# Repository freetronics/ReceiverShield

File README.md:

Freetronics 315MHz / 433MHz Receiver Shield
===========================================
Copyright 2011 Freetronics Pty Ltd  
Freetronics site:  <www.freetronics.com>  
Freetronics email: <info@freetronics.com>  

A general-purpose 315MHz / 433MHz receiver shield for the Arduino
and other microcontroller boards based on the same header format, such
as the Freetronics Eleven.

Includes significant prototyping area using the spare shield area.

Note that this design uses 0603 surface-mount parts and is intended for
machine assembly, but could still be assembled by hand with a fine-tip
soldering iron, a steady hand, and some magnification.

Features:

 * Reset button wired through to Arduino reset pin.
 * Two general-purpose surface-mount LEDs wired to GND via current-
   limiting resistors (drive HIGH to illuminate).
 * Pads for 2 surface-mount 100nF smoothing capacitors.
 * Parts overlay on both the top and the bottom so you can see what you
   are connecting without turning the board over.

More information is available on our product page at:

  http://www.freetronics.com/receiver

The "docs" folder within this repository includes a handy copy of the
schematic in PDF format and the Getting Started guide.

INSTALLATION
------------
The design is saved as an EAGLE project. EAGLE PCB design software is
available from www.cadsoftusa.com free for non-commercial use. To use
this project download it and place the directory containing these files
into the "eagle" directory on your computer. Then open EAGLE and
navigate to Projects -> eagle -> ReceiverShield.

DISTRIBUTION
------------
The specific terms of distribution of this project are governed by the
license referenced below.

LICENSE
-------
Licensed under the TAPR Open Hardware License (www.tapr.org/OHL).
The "license" folder within this repository also contains a copy of
this license in plain text format.

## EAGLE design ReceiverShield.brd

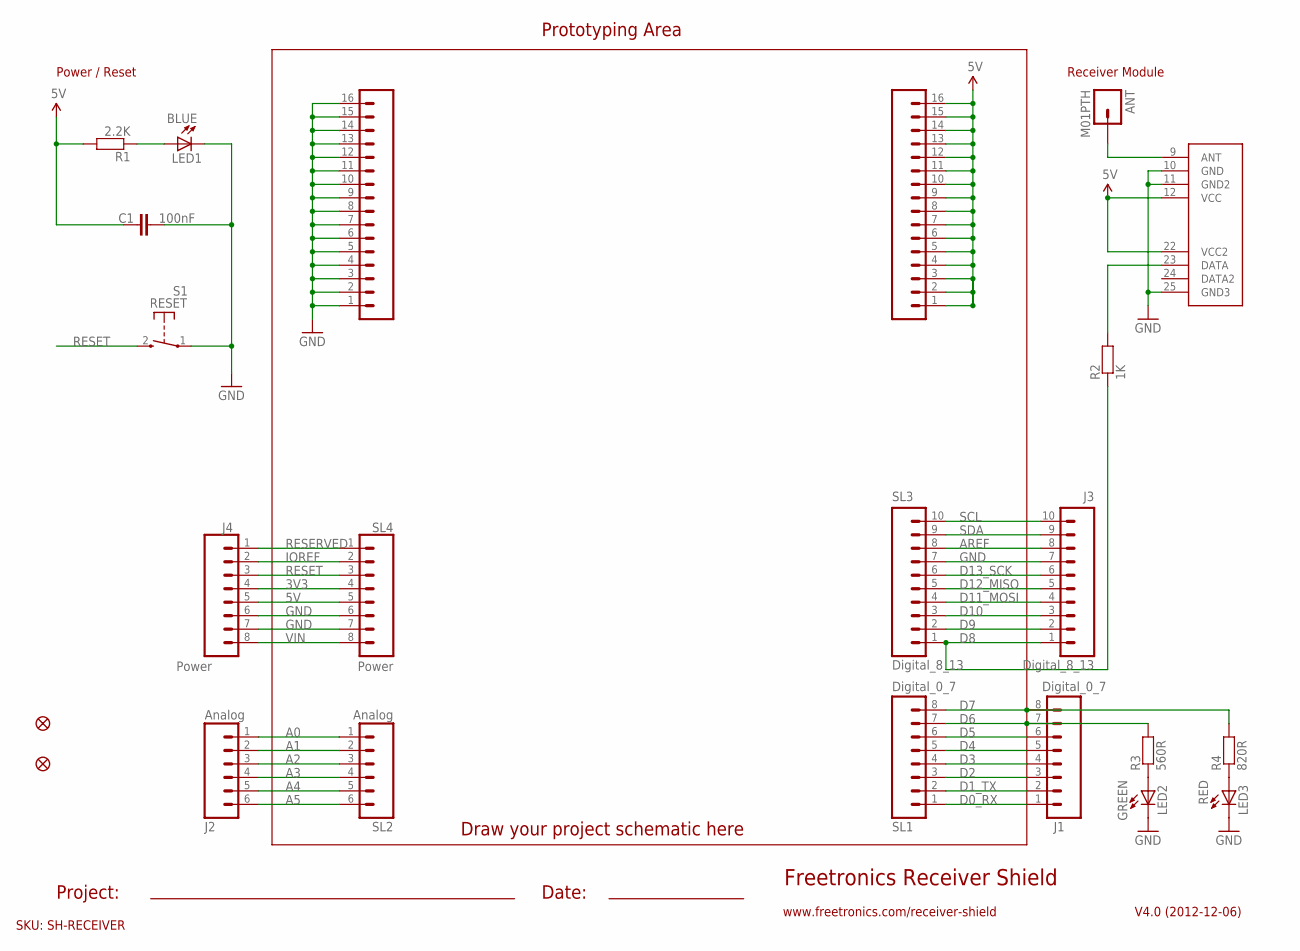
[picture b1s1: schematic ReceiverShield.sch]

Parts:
ANT: M01PTH; 1X01
C1: 100nF; 0603
J1: Digital_0_7; 1X08
J2: Analog; 1X06
J3: Digital_8_13; 1X10
J4: Power; 1X08
LED1: BLUE; LED-0603
LED2: GREEN; LED-0603
LED3: RED; LED-0603
PADS_5V: M16PTH; 1X16
PADS_GND: M16PTH; 1X16
R1: 2.2K; 0603
R2: 1K; 0603
R3: 560R; 0603
R4: 820R; 0603
RX1: RXB1SIL; RX-B1
S1: RESET; TACTILE_SWITCH_SMD_2PIN_TINY
SL1: Digital_0_7; 1X08
SL2: Analog; 1X06
SL3: Digital_8_13; 1X10
SL4: Power; 1X08
U$4, U$5: FIDUCIAL1X2.5; FIDUCIAL-1X2.5

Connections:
3V3: J4.4, SL4.4
5V: C1.1, J4.5, PADS_5V.1, PADS_5V.2, PADS_5V.3, PADS_5V.4, PADS_5V.5, PADS_5V.6, PADS_5V.7, PADS_5V.8, PADS_5V.9, PADS_5V.10, PADS_5V.11, PADS_5V.12, PADS_5V.13, PADS_5V.14, PADS_5V.15, PADS_5V.16, R1.2, RX1.12 (VCC), RX1.22 (VCC2), SL4.5
A0: J2.1, SL2.1
A1: J2.2, SL2.2
A2: J2.3, SL2.3
A3: J2.4, SL2.4
A4: J2.5, SL2.5
A5: J2.6, SL2.6
AREF: J3.8, SL3.8
D0_RX: J1.1, SL1.1
D1_TX: J1.2, SL1.2
D2: J1.3, SL1.3
D3: J1.4, SL1.4
D4: J1.5, SL1.5
D5: J1.6, SL1.6
D6: J1.7, R3.2, SL1.7
D7: J1.8, R4.2, SL1.8
D8: J3.1, R2.1, SL3.1
D9: J3.2, SL3.2
D10: J3.3, SL3.3
D11_MOSI: J3.4, SL3.4
D12_MISO: J3.5, SL3.5
D13_SCK: J3.6, SL3.6
GND: C1.2, J3.7, J4.6, J4.7, LED1.C, LED2.C, LED3.C, PADS_GND.1, PADS_GND.2, PADS_GND.3, PADS_GND.4, PADS_GND.5, PADS_GND.6, PADS_GND.7, PADS_GND.8, PADS_GND.9, PADS_GND.10, PADS_GND.11, PADS_GND.12, PADS_GND.13, PADS_GND.14, PADS_GND.15, PADS_GND.16, RX1.10 (GND), RX1.11 (GND2), RX1.25 (GND3), S1.1, SL3.7, SL4.6, SL4.7
IOREF: J4.2, SL4.2
unnamed: LED1.A, R1.1
unnamed: LED2.A, R3.1
unnamed: LED3.A, R4.1
unnamed: ANT.1, RX1.9 (ANT)
unnamed: R2.2, RX1.23 (DATA)
RESERVED: J4.1, SL4.1
RESET: J4.3, S1.2 (S), SL4.3
SCL: J3.10, SL3.10
SDA: J3.9, SL3.9
VIN: J4.8, SL4.8

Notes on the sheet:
Prototyping Area
Freetronics Receiver Shield
SKU: SH-RECEIVER
V4.0 (2012-12-06)
Power / Reset
Draw your project schematic here
Project:
Date:
Receiver Module
www.freetronics.com/receiver-shield

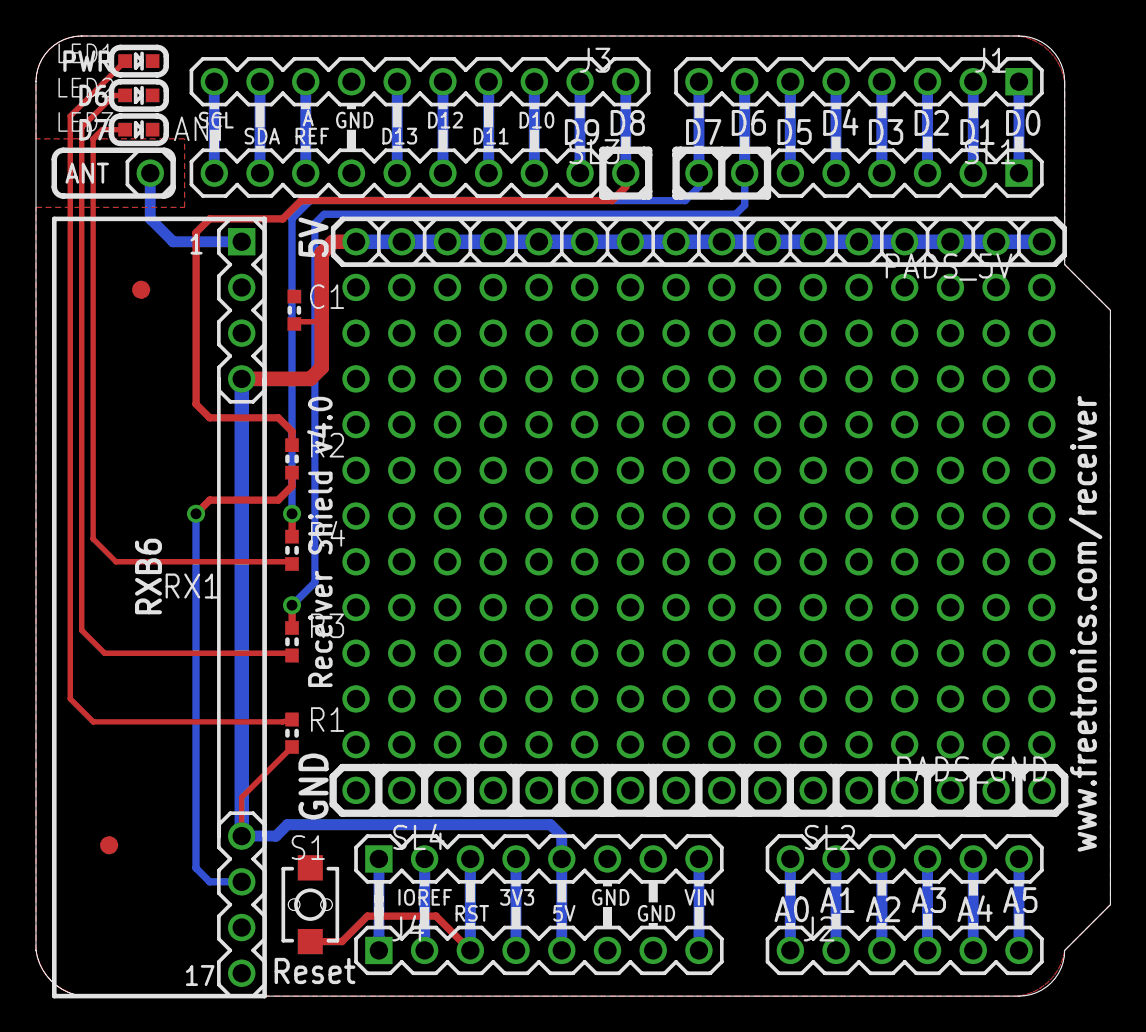
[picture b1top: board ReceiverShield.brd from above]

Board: 2 copper layers, 59.7 x 53.3 mm, 23 parts (0 on the bottom side), 35 nets.

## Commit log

2010-11-01 Initial import of v3 files
2011-04-20 Updated docs and project for release version
2012-12-06 Version 4.0 release with R3 headers
2019-04-24 Fix privileges

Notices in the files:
ReceiverShield.brd:
(C)2012 Freetronics Pty Ltd
